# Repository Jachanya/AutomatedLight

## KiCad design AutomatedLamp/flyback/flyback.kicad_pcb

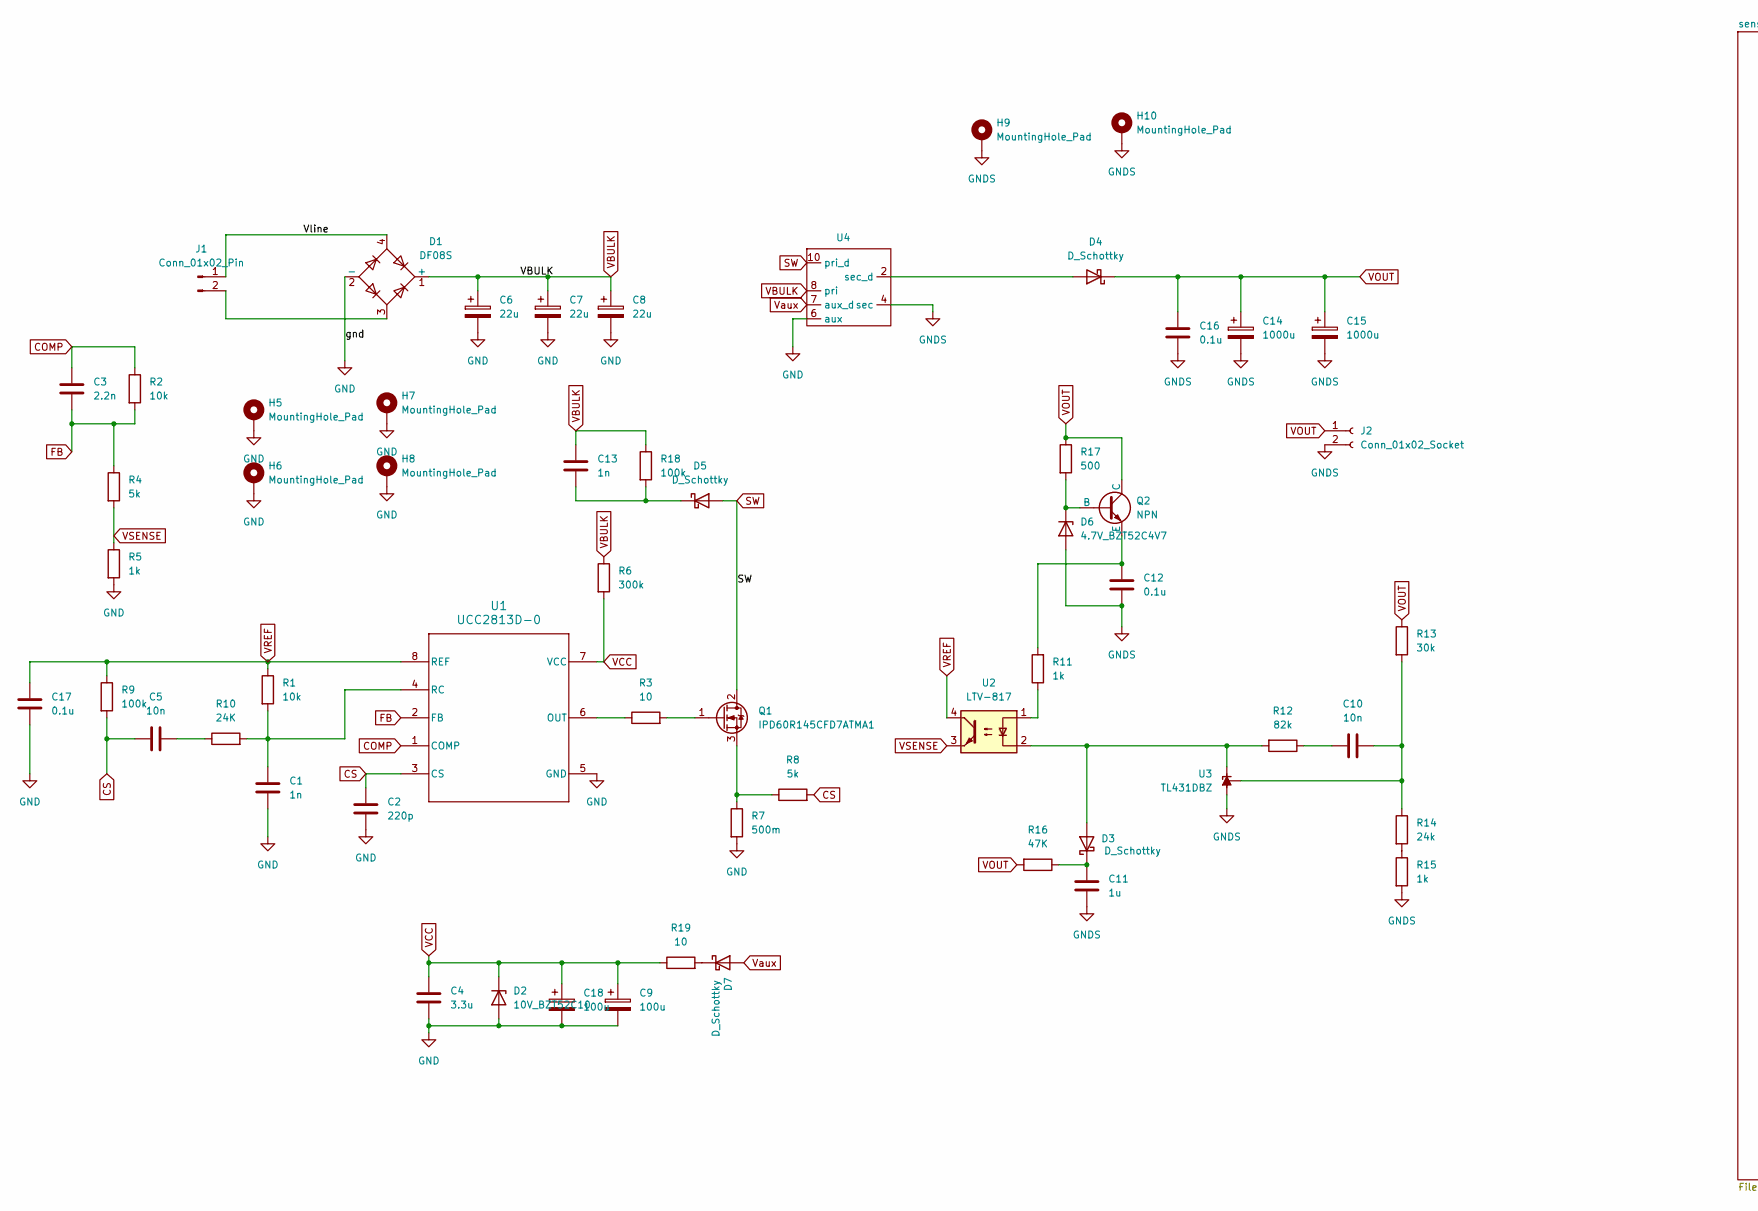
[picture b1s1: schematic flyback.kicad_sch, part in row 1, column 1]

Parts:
C1, C13: 1n; C_0805_2012Metric_Pad1.18x1.45mm_HandSolder
C2: 220p; C_0805_2012Metric_Pad1.18x1.45mm_HandSolder
C3: 2.2n; C_0805_2012Metric_Pad1.18x1.45mm_HandSolder
C4: 3.3u; C_1210_3225Metric_Pad1.33x2.70mm_HandSolder
C5, C10: 10n; C_0805_2012Metric_Pad1.18x1.45mm_HandSolder
C6, C7, C8: 22u; C_Radial_D12.5mm_H20.0mm_P5.00mm
C9, C18: 100u; CP_Elec_6.3x9.9
C11: 1u; C_1210_3225Metric_Pad1.33x2.70mm_HandSolder
C12, C16, C17: 0.1u; C_1210_3225Metric_Pad1.33x2.70mm_HandSolder
C14, C15: 1000u; CP_Elec_6.3x5.8
D1: DF08S; Diode_Bridge_OnSemi_SDIP-4L
D2: 10V_BZT52C10; Nexperia_CFP3_SOD-123W
D3, D7: D_Schottky; Nexperia_CFP3_SOD-123W
D4, D5: D_Schottky; D_SMA
D6: 4.7V_BZT52C4V7; Nexperia_CFP3_SOD-123W
H5, H6, H7, H8, H9, H10: MountingHole_Pad; MountingHole_3mm_Pad_Via
J1: Conn_01x02_Pin; TerminalBlock_bornier-2_P5.08mm
J2: Conn_01x02_Socket; PinSocket_2x01_P2.00mm_Vertical
Q1: IPD60R145CFD7ATMA1; TO-252-2
Q2: NPN; TSOT-23_HandSoldering
R1, R2: 10k; R_0805_2012Metric_Pad1.20x1.40mm_HandSolder
R3, R19: 10; R_0805_2012Metric_Pad1.20x1.40mm_HandSolder
R4, R8: 5k; R_0805_2012Metric_Pad1.20x1.40mm_HandSolder
R5, R11, R15: 1k; R_0805_2012Metric_Pad1.20x1.40mm_HandSolder
R6: 300k; R_0805_2012Metric_Pad1.20x1.40mm_HandSolder
R7: 500m; R_0805_2012Metric_Pad1.20x1.40mm_HandSolder
R9, R18: 100k; R_0805_2012Metric_Pad1.20x1.40mm_HandSolder
R10: 24K; R_0805_2012Metric_Pad1.20x1.40mm_HandSolder
R12: 82k; R_0805_2012Metric_Pad1.20x1.40mm_HandSolder
R13: 30k; R_0805_2012Metric_Pad1.20x1.40mm_HandSolder
R14: 24k; R_0805_2012Metric_Pad1.20x1.40mm_HandSolder
R16: 47K; R_0805_2012Metric_Pad1.20x1.40mm_HandSolder
R17: 500; R_0805_2012Metric_Pad1.20x1.40mm_HandSolder
U1: UCC2813D-0; D0008A_L
U2: LTV-817; DIP-4_W7.62mm
U3: TL431DBZ; SOT-23
U4: transformer

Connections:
/Vline: D1.4, J1.1
COMP: C3.1, R2.1, U1.1 (COMP)
CS: C2.1, C5.2, R8.2, R9.2, U1.3 (CS)
FB: C3.2, R2.2, R4.1, U1.2 (FB)
GND: C1.2, C2.2, C4.2, C6.2, C7.2, C8.2, C9.2, C17.2, C18.2, D1.2 (-), D2.2 (A), H5.1, H6.1, H7.1, H8.1, R5.2, R7.2, U1.5 (GND), U4.6 (aux)
GNDS: C11.2, C12.2, C14.2, C15.2, C16.2, D6.2 (A), H9.1, H10.1, J2.2, R15.2, U3.3 (A), U4.4 (sec); also elsewhere on the board
unnamed: C5.1, R10.1
unnamed: C10.1, R12.1
unnamed: D3.2 (A), R12.2, U2.2, U3.1 (K)
unnamed: C11.1, D3.1 (K), R16.1
unnamed: D4.2 (A), U4.2 (sec_d)
unnamed: C13.2, D5.1 (K), R18.2
unnamed: D6.1 (K), Q2.2 (B), R17.2
unnamed: D7.1 (K), R19.2
unnamed: D1.3, J1.2
unnamed: Q1.1 (G), R3.2
unnamed: Q1.3 (S), R7.1, R8.1
unnamed: C12.1, Q2.3 (E), R11.2
unnamed: R11.1, U2.1
unnamed: R14.2, R15.1
unnamed: R3.1, U1.6 (OUT)
unnamed: C1.1, R1.2, R10.2, U1.4 (RC)
unnamed: C10.2, R13.2, R14.1, U3.2 (REF)
SW: D5.2 (A), Q1.2 (D), U4.10 (pri_d)
VBULK: C6.1, C7.1, C8.1, C13.1, D1.1 (+), R6.1, R18.1, U4.8 (pri)
VCC: C4.1, C9.1, C18.1, D2.1 (K), R6.2, R19.1, U1.7 (VCC)
VOUT: C14.1, C15.1, C16.1, D4.1 (K), J2.1, Q2.1 (C), R13.1, R16.2, R17.1; also elsewhere on the board
VREF: C17.1, R1.1, R9.1, U1.8 (REF), U2.4
VSENSE: R4.2, R5.1, U2.3
Vaux: D7.2 (A), U4.7 (aux_d)

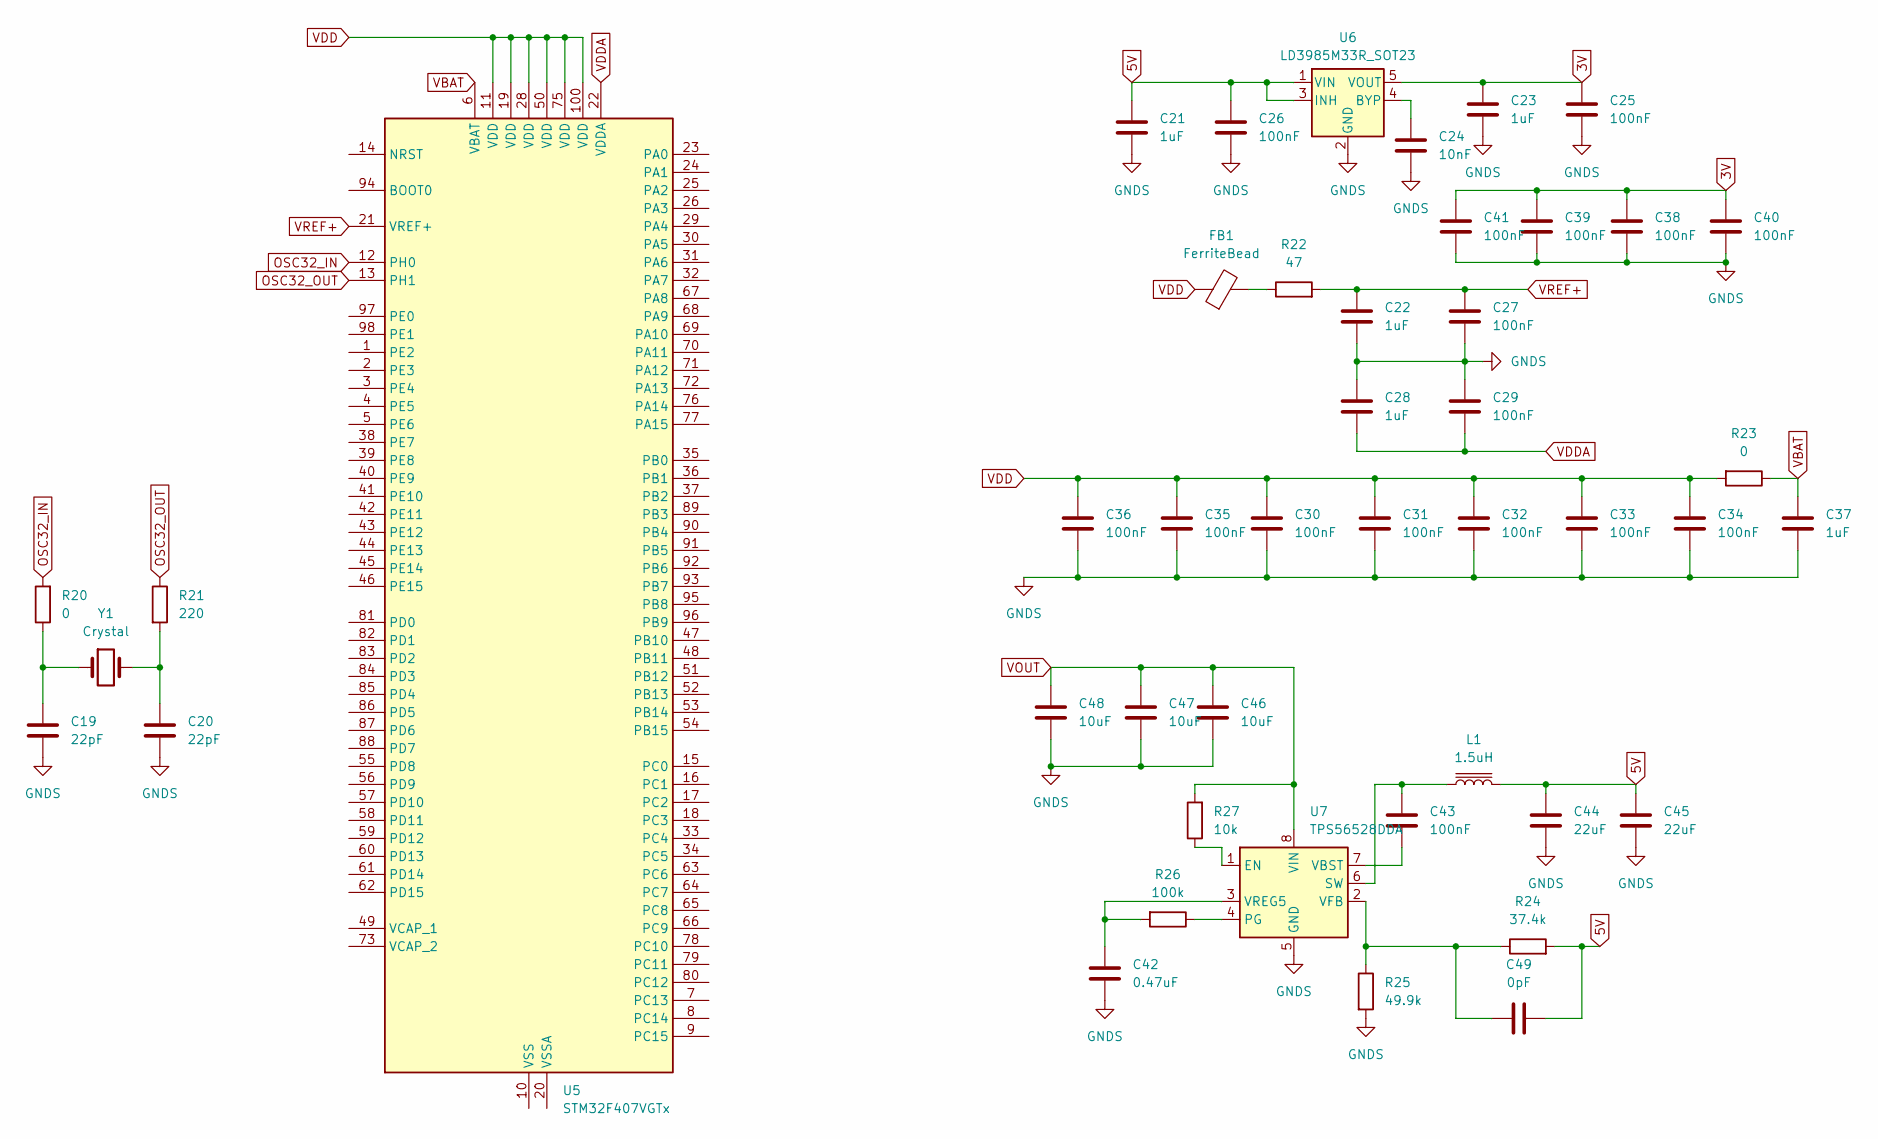
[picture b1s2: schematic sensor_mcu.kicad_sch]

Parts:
C19, C20: 22pF; C_0805_2012Metric_Pad1.18x1.45mm_HandSolder
C21, C22, C23, C28, C37: 1uF; C_1206_3216Metric_Pad1.33x1.80mm_HandSolder
C24: 10nF; C_1206_3216Metric_Pad1.33x1.80mm_HandSolder
C25, C26, C27, C29, C30, C31, C32, C33, C34, C35, C36, C38, C39, C40, C41, C43: 100nF; C_1206_3216Metric_Pad1.33x1.80mm_HandSolder
C42: 0.47uF; C_1206_3216Metric_Pad1.33x1.80mm_HandSolder
C44, C45: 22uF; C_1210_3225Metric_Pad1.33x2.70mm_HandSolder
C46, C47, C48: 10uF; C_1210_3225Metric_Pad1.33x2.70mm_HandSolder
C49: 0pF; C_0805_2012Metric_Pad1.18x1.45mm_HandSolder
FB1: FerriteBead; L_0805_2012Metric_Pad1.05x1.20mm_HandSolder
L1: 1.5uH; L_2512_6332Metric_Pad1.52x3.35mm_HandSolder
R20, R23: 0; R_0805_2012Metric_Pad1.20x1.40mm_HandSolder
R21: 220; R_0805_2012Metric_Pad1.20x1.40mm_HandSolder
R22: 47; R_0805_2012Metric_Pad1.20x1.40mm_HandSolder
R24: 37.4k; R_0805_2012Metric_Pad1.20x1.40mm_HandSolder
R25: 49.9k; R_0805_2012Metric_Pad1.20x1.40mm_HandSolder
R26: 100k; R_0805_2012Metric_Pad1.20x1.40mm_HandSolder
R27: 10k; R_0805_2012Metric_Pad1.20x1.40mm_HandSolder
U5: STM32F407VGTx; LQFP-100_14x14mm_P0.5mm
U6: LD3985M33R_SOT23; SOT-23-5
U7: TPS56528DDA; Texas_HSOP-8-1EP_3.9x4.9mm_P1.27mm_ThermalVias
Y1: Crystal; Crystal_HC49-4H_Vertical

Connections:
3V: C23.1, C25.1, C38.1, C39.1, C40.1, C41.1, U6.5 (VOUT)
5V: C21.1, C26.1, C44.1, C45.1, C49.2, L1.2, R24.2, U6.1 (VIN), U6.3 (INH)
GNDS: C19.2, C20.2, C21.2, C22.2, C23.2, C24.2, C25.2, C26.2, C27.2, C28.1, C29.1, C30.2, C31.2, C32.2, C33.2, C34.2, C35.2, C36.2, C37.2, C38.2, C39.2, C40.2, C41.2, C42.2, C44.2, C45.2, C46.2, C47.2, C48.2, R25.2, U6.2 (GND), U7.5 (GND), U7.9 (GND); also elsewhere on the board
unnamed: C19.1, R20.1, Y1.1
unnamed: C20.1, R21.2, Y1.2
unnamed: FB1.2, R22.1
unnamed: U5.10 (VSS), U5.27 (VSS), U5.74 (VSS), U5.99 (VSS)
unnamed: C24.1, U6.4 (BYP)
unnamed: R27.1, U7.1 (EN)
unnamed: R26.1, U7.4 (PG)
unnamed: C43.2, L1.1, U7.6 (SW)
unnamed: C43.1, U7.7 (VBST)
unnamed: C49.1, R24.1, R25.1, U7.2 (VFB)
unnamed: C42.1, R26.2, U7.3 (VREG5)
OSC32_IN: R20.2, U5.12 (PH0)
OSC32_OUT: R21.1, U5.13 (PH1)
VBAT: C37.1, R23.1, U5.6 (VBAT)
VDD: C30.1, C31.1, C32.1, C33.1, C34.1, C35.1, C36.1, FB1.1, R23.2, U5.11 (VDD), U5.19 (VDD), U5.28 (VDD), U5.50 (VDD), U5.75 (VDD), U5.100 (VDD)
VDDA: C28.2, C29.2, U5.22 (VDDA)
VOUT: C46.1, C47.1, C48.1, R27.2, U7.8 (VIN); also elsewhere on the board
VREF+: C22.1, C27.1, R22.2, U5.21 (VREF+)

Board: 4 copper layers, 103 parts (45 on the bottom side), 49 nets, no tracks yet.

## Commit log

2025-05-21 Kicad lamp controller project
